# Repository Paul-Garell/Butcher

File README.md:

# Butcher Lab Cervicheck project

Questions, reach out to George Zeng (gz266@cornell.edu). 

This contains the code to run on Arduino Uno/Due to calculate frequency sweeps using the AD5933 chip.

This repo also will contain the code for communication between the Rasberry pi and Arduino. 

PCB board designs can be found under hardware. 

Uno code (working) can be found under Arduino

Raspberry Pi information can be found under RasPi

Contains code to analyze and present data

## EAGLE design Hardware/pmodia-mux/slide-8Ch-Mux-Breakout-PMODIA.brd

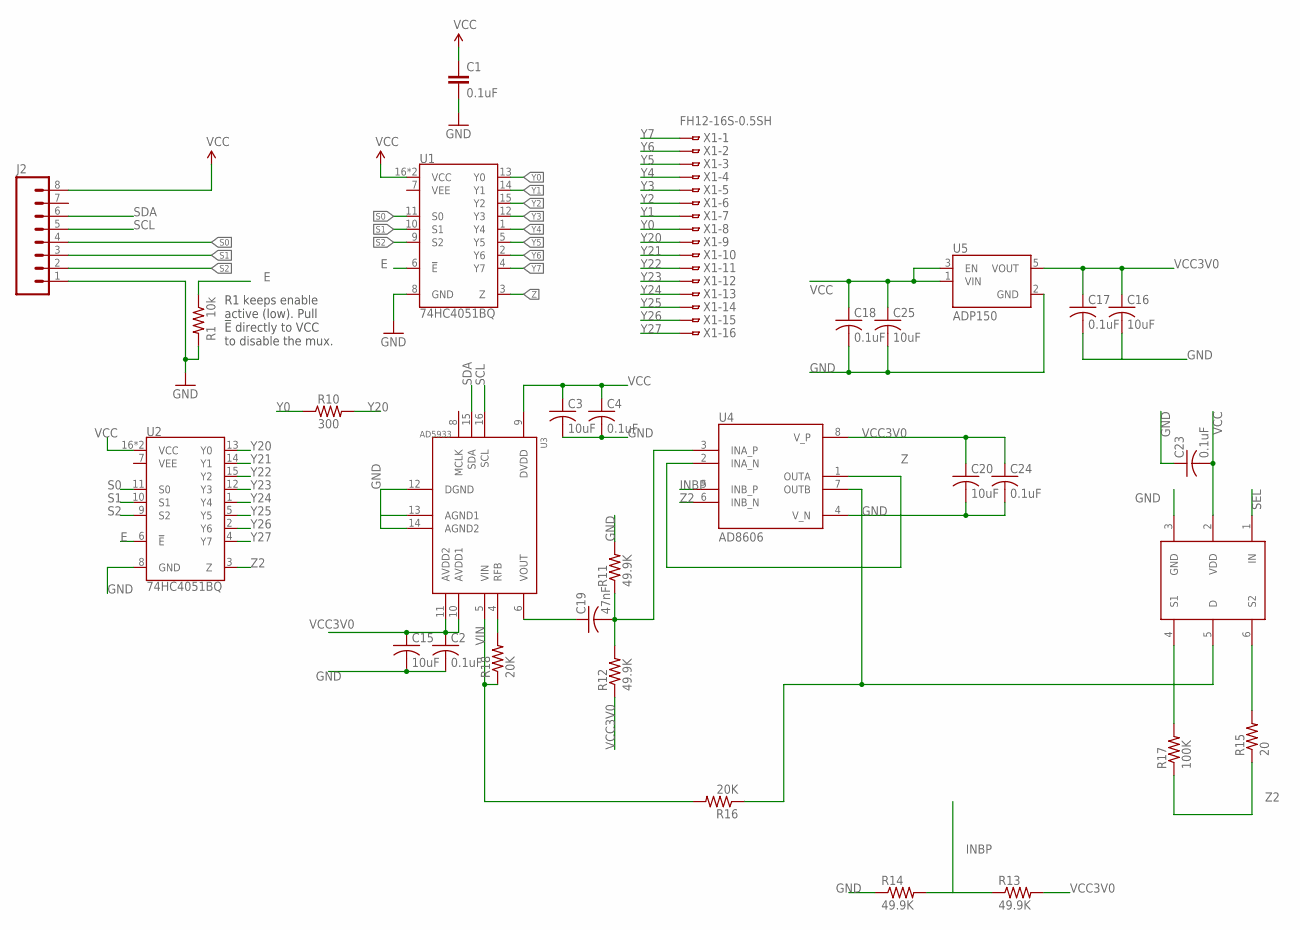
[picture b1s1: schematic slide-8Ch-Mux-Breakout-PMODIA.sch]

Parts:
C1: 0.1uF; 0603
C2, C4, C17, C18, C23, C24: 0.1uF; C0805K
C3, C15, C16, C20, C25: 10uF; C0805K
C19: 47nF; C0805K
J2: M08; 1X08_ROUND
R1: 10k; 0603
R10: 300; 0805
R11, R12, R13, R14: 49.9K; R0603
R15: 20; R0603
R16, R18: 20K; R0603
R17: 100K; R0603
U1, U2: 74HC4051BQ; DHVQFN-16-2.5X3.5MM
U3: AD5933; SSOP16
U4: AD8606; SOIC-8
U5: ADP150; SOT95P280X100-5N
U$1: ADG849THROUHG_HOLE; SOT65P210X110-6N
X1: FH12-16S-0.5SH

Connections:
E: R1.1, U1.6 (!E!), U2.6 (!E!)
GND: C1.2, C2.2, C3.2, C4.2, C15.2, C16.2, C17.2, C18.2, C20.2, C23.1, C24.2, C25.2, J2.1, R1.2, R11.2, R14.1, U1.8 (GND), U2.8 (GND), U3.12 (DGND), U3.14 (AGND2), U4.4 (V_N), U5.2 (GND), U$1.3 (GND)
INBP: R13.1, R14.2, U4.5 (INB_P)
unnamed: C19.1, U3.6 (VOUT)
unnamed: C19.2, R11.1, R12.2, U4.3 (INA_P)
unnamed: R18.2, U3.4 (RFB)
unnamed: R15.2, U$1.6 (S2)
unnamed: R17.2, U$1.4 (S1)
unnamed: R16.1, U4.7 (OUTB), U$1.5 (D)
S0: J2.4, U1.11 (S0), U2.11 (S0)
S1: J2.3, U1.10 (S1), U2.10 (S1)
S2: J2.2, U1.9 (S2), U2.9 (S2)
SCL: J2.5, U3.16 (SCL)
SDA: J2.6, U3.15 (SDA)
SEL: U$1.1 (IN)
VCC: C1.1, C3.1, C4.1, C18.1, C23.2, C25.1, J2.8, U1.16 (VCC), U1.EP (VCC), U2.16 (VCC), U2.EP (VCC), U3.9 (DVDD), U5.1 (VIN), U5.3 (EN), U$1.2 (VDD)
VCC3V0: C2.1, C15.1, C16.1, C17.1, C20.1, C24.1, R12.1, R13.2, U3.10 (AVDD1), U3.11 (AVDD2), U4.8 (V_P), U5.5 (VOUT)
VIN: R16.2, R18.1, U3.5 (VIN)
Y0: R10.1, U1.13 (Y0), X1.8
Y1: U1.14 (Y1), X1.7
Y2: U1.15 (Y2), X1.6
Y3: U1.12 (Y3), X1.5
Y4: U1.1 (Y4), X1.4
Y5: U1.5 (Y5), X1.3
Y6: U1.2 (Y6), X1.2
Y7: U1.4 (Y7), X1.1
Y20: R10.2, U2.13 (Y0), X1.9
Y21: U2.14 (Y1), X1.10
Y22: U2.15 (Y2), X1.11
Y23: U2.12 (Y3), X1.12
Y24: U2.1 (Y4), X1.13
Y25: U2.5 (Y5), X1.14
Y26: U2.2 (Y6), X1.15
Y27: U2.4 (Y7), X1.16
Z: U1.3 (Z), U4.1 (OUTA), U4.2 (INA_N)
Z2: R15.1, R17.1, U2.3 (Z), U4.6 (INB_N)

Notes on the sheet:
R1 keeps enable active (low). Pull !E! directly to VCC to disable the mux.

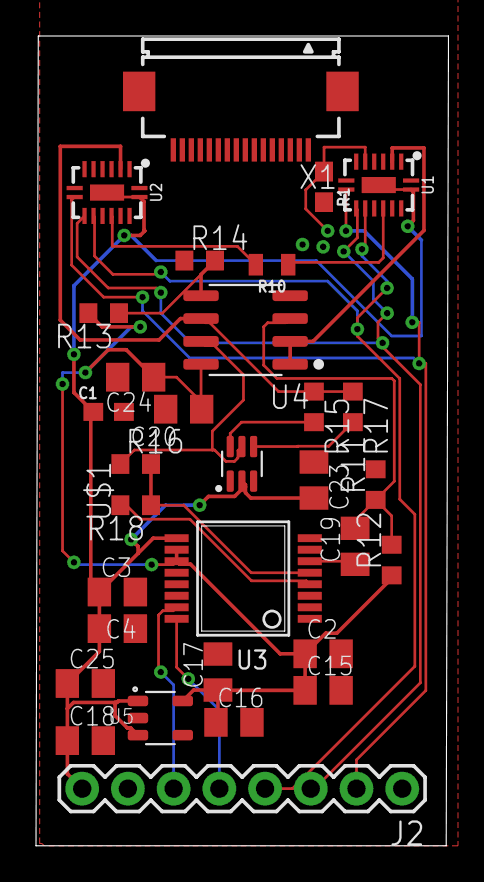
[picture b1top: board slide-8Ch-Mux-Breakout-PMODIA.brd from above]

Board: 2 copper layers, 22.9 x 45.0 mm, 31 parts (0 on the bottom side), 35 nets.

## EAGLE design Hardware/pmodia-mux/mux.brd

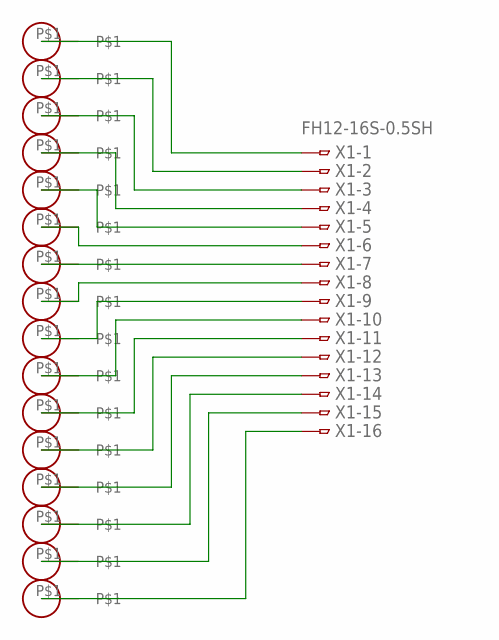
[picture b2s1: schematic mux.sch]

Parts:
U$1, U$2, U$3, U$4, U$5, U$6, U$7, U$8, U$9, U$10, U$11, U$12, U$13, U$14, U$15, U$16: PADPAD; PAD
X1: FH12-16S-0.5SH

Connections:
unnamed 1: U$1.P$1, X1.1; also elsewhere on the board
unnamed 2: U$2.P$1, X1.2; also elsewhere on the board
unnamed 3: U$3.P$1, X1.3; also elsewhere on the board
unnamed 4: U$4.P$1, X1.4; also elsewhere on the board
unnamed 5: U$5.P$1, X1.5; also elsewhere on the board
unnamed 6: U$6.P$1, X1.6; also elsewhere on the board
unnamed 7: U$7.P$1, X1.7; also elsewhere on the board
unnamed 8: U$8.P$1, X1.8; also elsewhere on the board
unnamed 9: U$9.P$1, X1.9; also elsewhere on the board
unnamed 10: U$10.P$1, X1.10; also elsewhere on the board
unnamed 11: U$11.P$1, X1.11; also elsewhere on the board
unnamed 12: U$12.P$1, X1.12; also elsewhere on the board
unnamed 13: U$13.P$1, X1.13; also elsewhere on the board
unnamed 14: U$14.P$1, X1.14; also elsewhere on the board
unnamed 15: U$15.P$1, X1.15; also elsewhere on the board
unnamed 16: U$16.P$1, X1.16; also elsewhere on the board

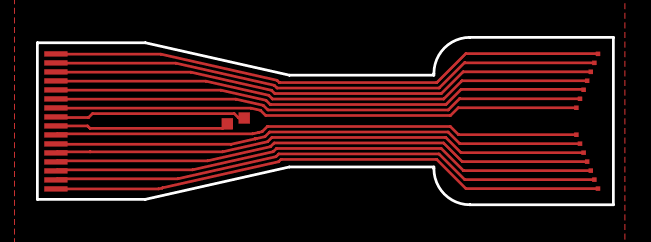
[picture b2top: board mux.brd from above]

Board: 2 copper layers, 32.0 x 9.3 mm, 17 parts (0 on the bottom side), 16 nets.

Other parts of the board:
X2: FH12-16S-0.5SH

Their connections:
unnamed 1: X2.1; also elsewhere on the board
unnamed 2: X2.2; also elsewhere on the board
unnamed 3: X2.3; also elsewhere on the board
unnamed 4: X2.4; also elsewhere on the board
unnamed 5: X2.5; also elsewhere on the board
unnamed 6: X2.6; also elsewhere on the board
unnamed 7: X2.7; also elsewhere on the board
unnamed 8: X2.8; also elsewhere on the board
unnamed 9: X2.9; also elsewhere on the board
unnamed 10: X2.10; also elsewhere on the board
unnamed 11: X2.11; also elsewhere on the board
unnamed 12: X2.12; also elsewhere on the board
unnamed 13: X2.13; also elsewhere on the board
unnamed 14: X2.14; also elsewhere on the board
unnamed 15: X2.15; also elsewhere on the board
unnamed 16: X2.16; also elsewhere on the board

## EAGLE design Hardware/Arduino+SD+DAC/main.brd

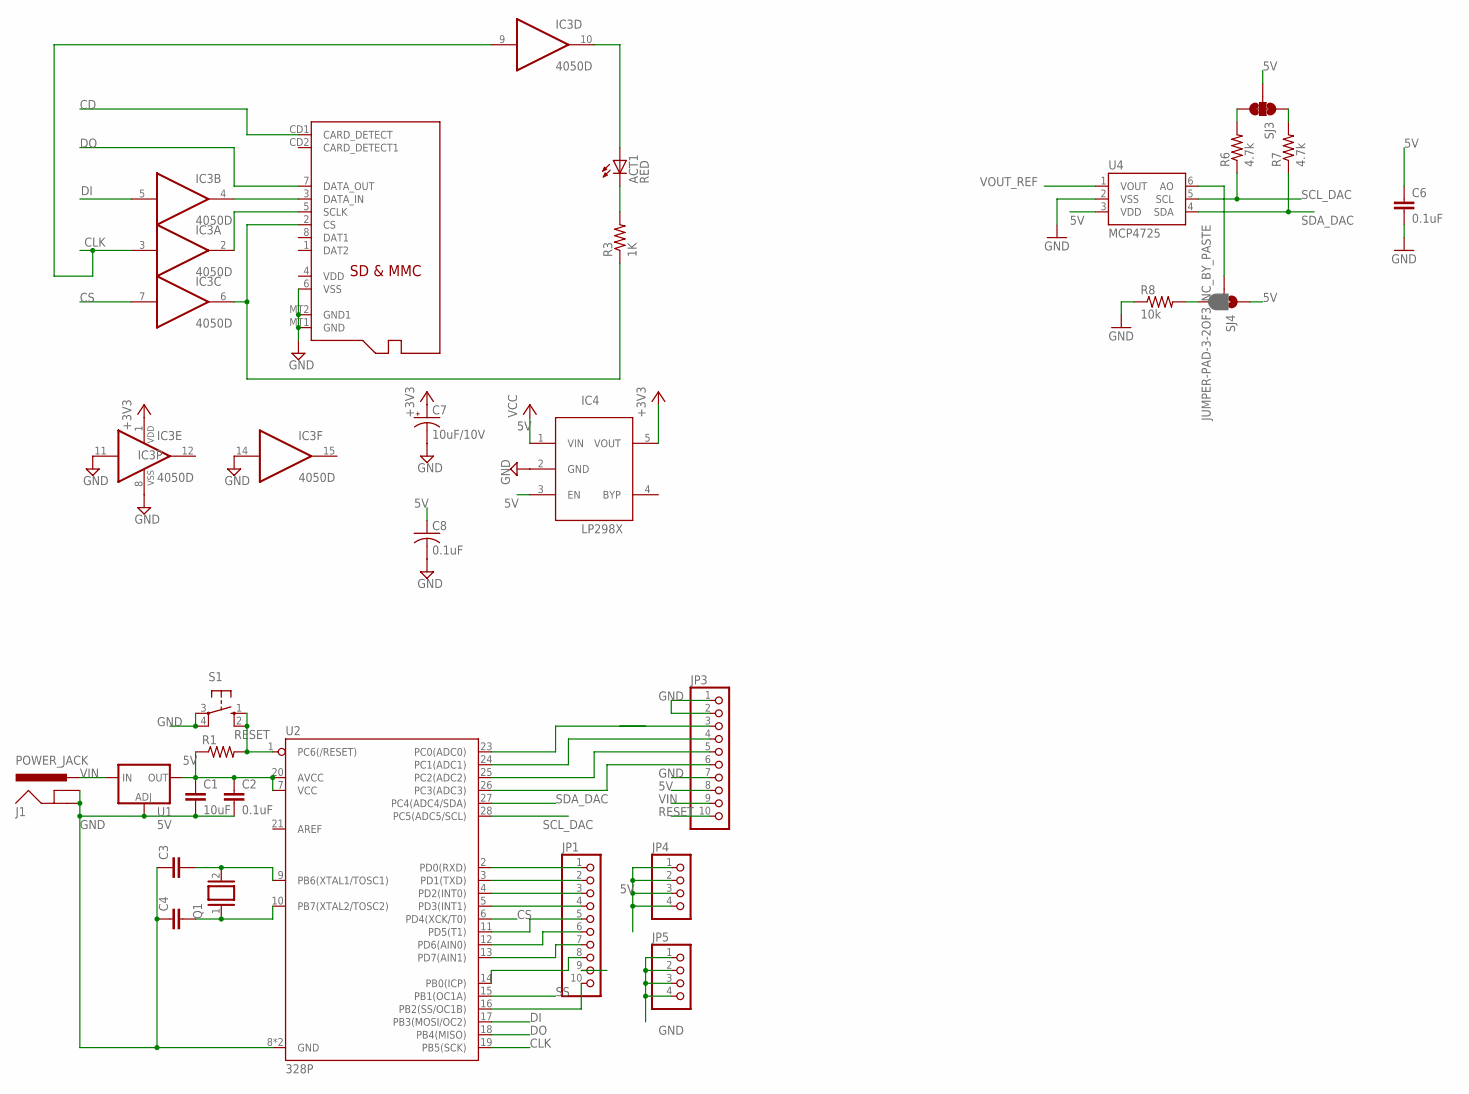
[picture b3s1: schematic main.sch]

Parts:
ACT1: RED; CHIP-LED0805
C1: 10uF; C025-024X044
C2: 0.1uF; C025-024X044
C3, C4: C-EU025-024X044; C025-024X044
C6: 0.1uF; 0603-CAP
C7: 10uF/10V; A/3216-18R
C8: 0.1uF; C0805K
IC3: 4050D; SO16
IC4: LP298XS; SOT23-5L
J1: POWER_JACK; POWER_JACK_PTH
JP1, JP3: PINHD-1X10; 1X10
JP4, JP5: PINHD-1X4; 1X04
Q1: XTAL/S; QS
R1: R-US_0204/7; 0204/7
R3: 1K; R0805
R6, R7: 4.7k; 0603-RES
R8: 10k; 0603-RES
S1: 10-XX; B3F-10XX
SJ3: JUMPER-PAD-3-NC_BY_TRACE; PAD-JUMPER-3-3OF3_NC_BY_TRACE_YES_SILK_FULL_BOX
SJ4: JUMPER-PAD-3-2OF3_NC_BY_PASTE; PAD-JUMPER-3-2OF3_NC_BY_PASTE_YES_SILK_FULL_BOX
U1: 5V; SOT223
U2: 328P; DIP28
U4: MCP4725; SOT23-6
X2: MICROSD

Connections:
5V: C1.1, C2.1, C6.1, C8.1, IC4.1 (VIN), IC4.3 (EN), JP3.8, JP4.1, JP4.2, JP4.3, JP4.4, R1.1, SJ3.2, SJ4.1, U1.2 (OUT), U1.4 (OUT), U2.7 (VCC), U2.20 (AVCC), U4.3 (VDD)
+3V3: C7.+, IC3.1 (VDD), IC4.5 (VOUT)
CD: X2.CD1 (CARD_DETECT)
CLK: IC3.3 (I), IC3.9 (I), U2.19 (PB5(SCK))
CS: IC3.7 (I), U2.6 (PD4(XCK/T0))
DI: IC3.5 (I), U2.17 (PB3(MOSI/OC2))
DO: U2.18 (PB4(MISO)), X2.7 (DATA_OUT)
GND: C1.2, C2.2, C3.1, C4.1, C6.2, C7.-, C8.2, IC3.8 (VSS), IC3.11 (I), IC3.14 (I), IC4.2 (GND), J1.GND, J1.GNDBREAK, JP3.1, JP3.2, JP3.7, JP5.1, JP5.2, JP5.3, JP5.4, R8.1, S1.3, S1.4 (P1), U1.1 (ADJ), U2.8 (GND), U2.22 (GND), U4.2 (VSS), X2.6 (VSS), X2.MT1 (GND), X2.MT2 (GND1)
unnamed: JP1.1, U2.2 (PD0(RXD))
unnamed: JP3.5, U2.25 (PC2(ADC2))
unnamed: C3.2, Q1.2, U2.9 (PB6(XTAL1/TOSC1))
unnamed: C4.2, Q1.1, U2.10 (PB7(XTAL2/TOSC2))
unnamed: JP1.2, U2.3 (PD1(TXD))
unnamed: JP1.3, U2.4 (PD2(INT0))
unnamed: JP3.6, U2.26 (PC3(ADC3))
unnamed: JP1.4, U2.5 (PD3(INT1))
unnamed: JP1.5, U2.11 (PD5(T1))
unnamed: R7.2, SJ3.1
unnamed: R6.2, SJ3.3
unnamed: SJ4.2, U4.6 (AO)
unnamed: R8.2, SJ4.3
unnamed: JP1.6, U2.12 (PD6(AIN0))
unnamed: JP1.7, U2.13 (PD7(AIN1))
unnamed: JP1.8, U2.14 (PB0(ICP))
unnamed: JP1.10, U2.16 (PB2(SS/OC1B))
unnamed: JP3.4, U2.24 (PC1(ADC1))
unnamed: ACT1.A, IC3.10 (O)
unnamed: IC3.2 (O), X2.5 (SCLK)
unnamed: IC3.6 (O), R3.1, X2.2 (CS)
unnamed: ACT1.C, R3.2
unnamed: IC3.4 (O), X2.3 (DATA_IN)
RESET: JP3.10, R1.2, S1.1 (S), S1.2 (S1), U2.1 (PC6(/RESET))
SCL_DAC: R6.1, U2.28 (PC5(ADC5/SCL)), U4.5 (SCL)
SDA_DAC: R7.1, U2.27 (PC4(ADC4/SDA)), U4.4 (SDA)
SS: JP1.9, U2.15 (PB1(OC1A))
VIN: J1.PWR, JP3.9, U1.3 (IN)
VOUT_REF: U4.1 (VOUT)

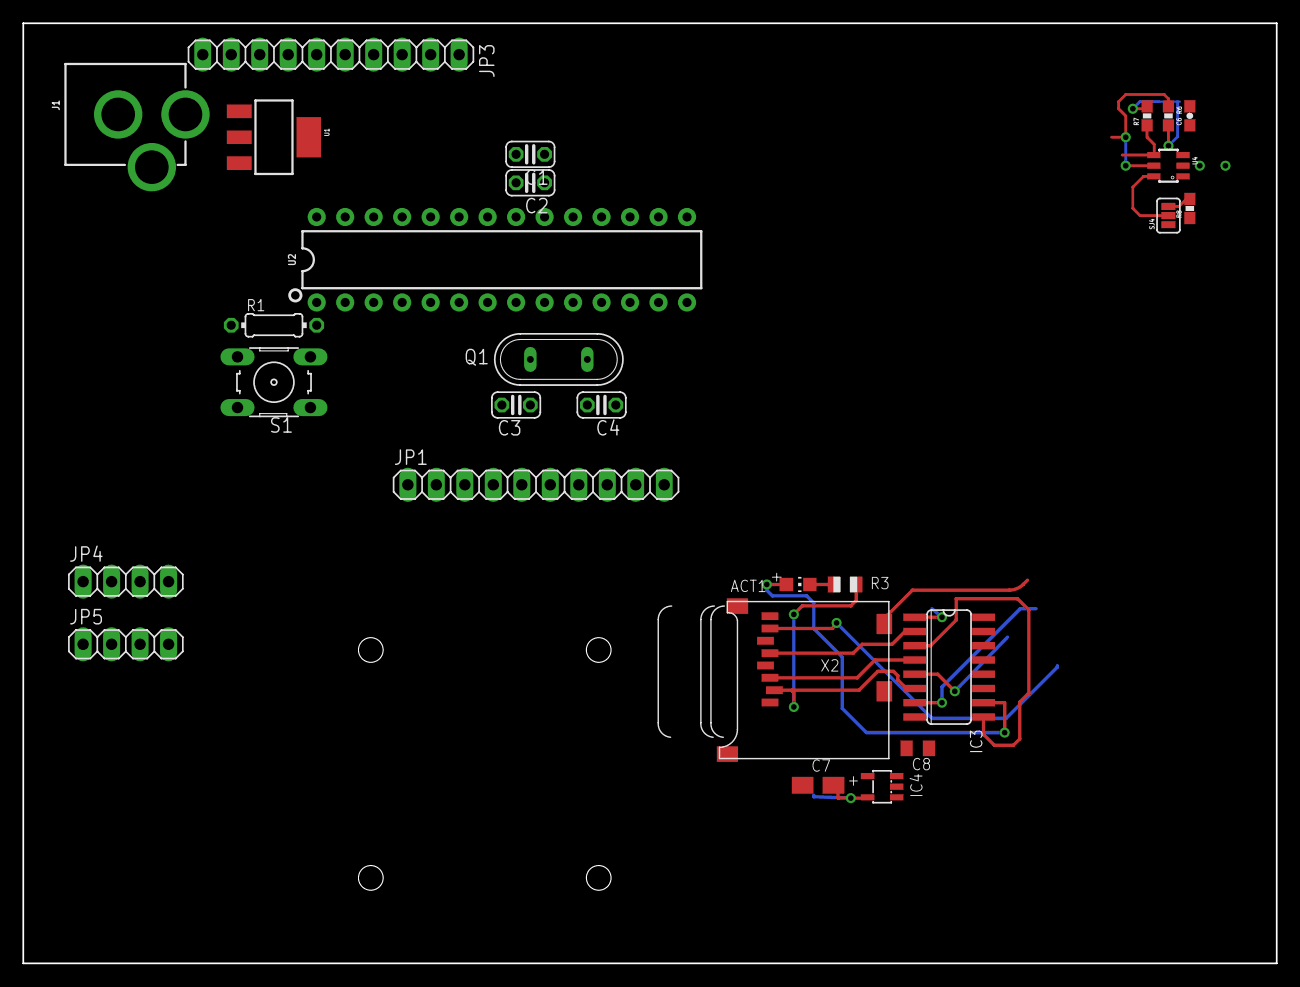
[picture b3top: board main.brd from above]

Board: 2 copper layers, 111.8 x 83.8 mm, 28 parts (1 on the bottom side), 35 nets.

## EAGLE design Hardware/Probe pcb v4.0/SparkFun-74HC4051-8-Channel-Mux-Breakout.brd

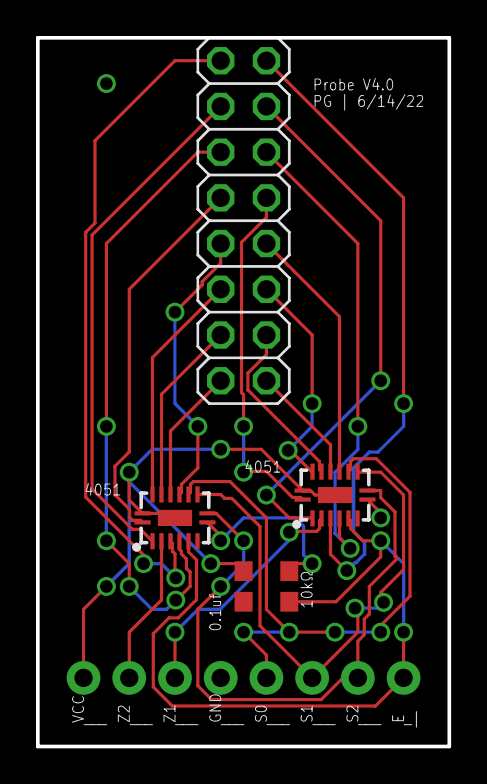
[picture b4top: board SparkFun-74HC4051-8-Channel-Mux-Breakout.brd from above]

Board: 2 copper layers, 22.9 x 39.4 mm, 6 parts (1 on the bottom side), 24 nets.

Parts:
C1: 0.1uF; 0603
J2: 1X08_ROUND
JP1: 2X08
R1: 10k; 0603
U1, U2: 74HC4051BQ; DHVQFN-16-2.5X3.5MM

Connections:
E: J2.1, R1.1, U1.6, U2.6
GND: C1.2, J2.5, R1.2, U1.8, U2.8
S0: J2.4, U1.11, U2.11
S1: J2.3, U1.10, U2.10
S2: J2.2, U1.9, U2.9
VCC: C1.1, J2.8, U1.16, U1.EP, U2.16, U2.EP
Y0: JP1.1, U1.13
Y1: JP1.3, U1.14
Y2: JP1.5, U1.15
Y3: JP1.7, U1.12
Y4: JP1.9, U1.1
Y5: JP1.11, U1.5
Y6: JP1.13, U1.2
Y7: JP1.15, U1.4
Y20: JP1.2, U2.13
Y21: JP1.4, U2.14
Y22: JP1.6, U2.15
Y23: JP1.8, U2.12
Y24: JP1.10, U2.1
Y25: JP1.12, U2.5
Y26: JP1.14, U2.2
Y27: JP1.16, U2.4
Z: J2.6, U1.3
Z2: J2.7, U2.3

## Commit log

2023-04-08 Setting up Repo
2023-06-20 Add Probe
2023-06-20 Add probe stl
2023-06-21 clean up code (no big changes yet)
2023-06-22 preliminary sd card code
2023-06-22 Update ad5933-test-new.ino
    change pin
2023-06-23 code for threshold
2023-06-23 new code
2023-06-23 Rename ad5933-test-new.ino to ad5933-test-csvino
2023-06-23 Rename ad5933-test-csvino to ad5933-test-csv.ino
2023-06-24 update threshold code
2023-06-25 edit threshold
2023-06-28 Update ad5933-test-sd.ino
    -added a time elapsed column, before impedance and after pressure columns
2023-07-08 rearrange fiels
2023-07-08 add ramchip
2023-07-08 change name
2023-07-08 sd card arrays
2023-07-10 Update ad5933-test-sd.ino
    -changed type initializations (bug)
2023-07-11 Update sd5933-test-threshold-sd.ino
    serial print statements for testing
2023-07-11 Update sd5933-test-threshold-sd.ino
    Commented out serial prints
2023-07-11 Update ad5933-test-threshold-sd2.ino
    Another version of threshold+SD code
2023-07-16 Create ad5933-test-threshold-array
2023-07-16 Update ad5933-test-threshold-array
2023-07-16 Update ad5933-test-threshold.ino
    add calibration
2023-07-18 Rename ad5933-test-threshold-array to ad5933-test-threshold-array.ino
2023-09-21 Restructure
2023-09-21 update layout
2023-10-19 [Update] start routing board
2023-10-19 [update] finished routing - should be optimized tho:
2023-11-02 Add files via upload
    pad library and mux schematic
2024-02-12 new Schematic
2024-02-15 Schematic
2024-02-20 Finished Flex PCB
2024-03-01 Updated names
2024-03-04 Routed
2024-03-07 Start main
2024-10-18 Create PressureSweepV1
2025-01-23 Create StressStrain_V1
2025-01-23 Create PressureSweep_V2
2025-01-23 Rename PressureSweepV1 to PressureSweepV1.ino
2025-01-23 Rename PressureSweep_V2 to PressureSweep_V2.ino
2025-01-23 Rename StressStrain_V1 to StressStrain_V1.ino

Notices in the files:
parts and their libraries:
SparkFun-Connectors: Licensing: Creative Commons ShareAlike 4.0 International - https://creativecommons.org/licenses/by-sa/4.0
